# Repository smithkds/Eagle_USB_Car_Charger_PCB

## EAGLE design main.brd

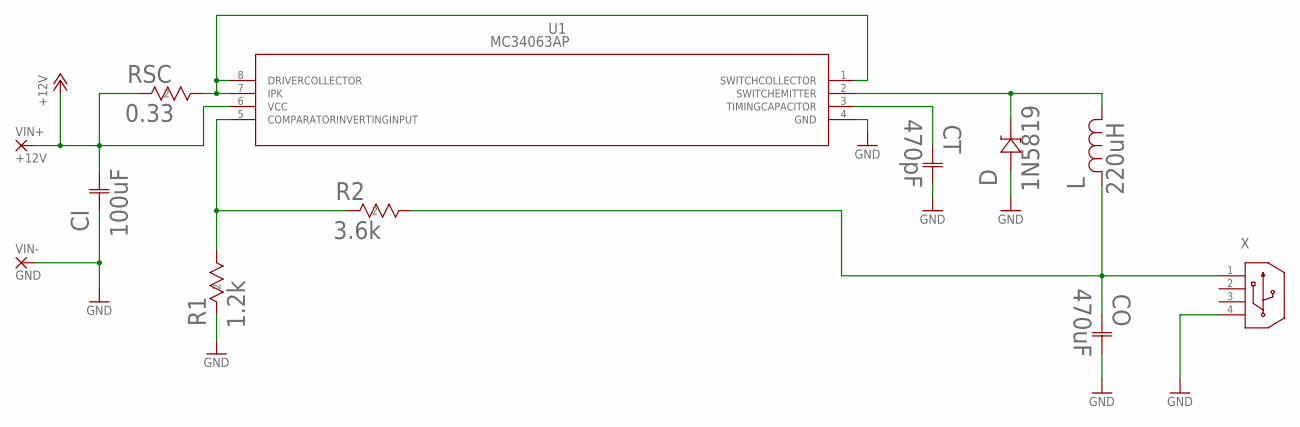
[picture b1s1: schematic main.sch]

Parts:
CI: 100uF; U1-I_NCH
CO: 470uF; U1-I_NCH
CT: 470pF; CAP_FA28_TDK
D: 1N5819; DO-41_STM
L: 220uH; IND_6000
R1: 1.2k; RES_MRS16_VIS
R2: 3.6k; STA_RNMF14_STP
RSC: 0.33; PF1262-0R33F1
U1: MC34063AP; P8
VIN+: +12V; 2,54/1,1
VIN-: GND; 2,54/1,1
X: 6364372-2; CONN_6364372-2_TEC

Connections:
+12V: CI.2, RSC.2, U1.6 (VCC), VIN+.1
GND: CI.1, CO.2, CT.2, D.2, R1.2, U1.4 (GND), VIN-.1, X.4
unnamed: CT.1, U1.3 (TIMINGCAPACITOR)
unnamed: D.1, L.1, U1.2 (SWITCHEMITTER)
unnamed: CO.1, L.2, R2.1, X.1
unnamed: RSC.1, U1.1 (SWITCHCOLLECTOR), U1.7 (IPK), U1.8 (DRIVERCOLLECTOR)
unnamed: R1.1, R2.2, U1.5 (COMPARATORINVERTINGINPUT)

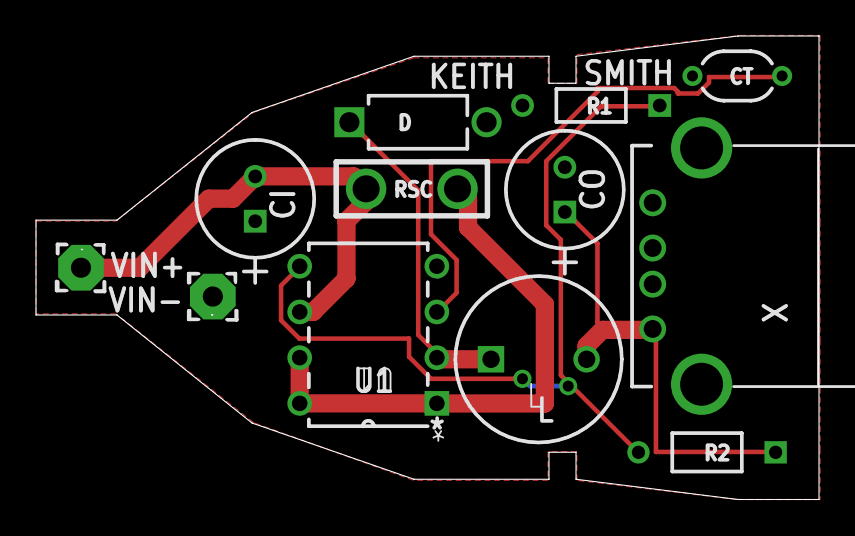
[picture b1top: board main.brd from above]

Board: 2 copper layers, 43.5 x 25.8 mm, 12 parts (0 on the bottom side), 7 nets.

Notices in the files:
parts and their libraries:
COPYRIGHT: Copyright (C) 2018 Accelerated Designs. All rights reserved
